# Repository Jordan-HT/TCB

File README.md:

# Thyristor Control Board (TCB) Project
By Jordan Harris-Toovy for internal and shared projects.
This repo contains the design files and accocated C/c++ code for a custom RP2040-powered dual thyristor control module. It is intended to be used to drive either two large SCRs as part of a SCR bridge rectifier, or a single large TriAC as the code of a larger power supply. Via an onboard current sensor, current measurements can be used in a feedback system if desired. Additionally, the I/O on the low-voltage side of the isolation barrier will allow for CNC integration for novel applications.

Currently, the board is in production of the first test batch, with an estimated arrival date of 2023-06-16. Code for the onboard Seeed XIAO RP2040 is also being developed, however, it is not yet ready. I will update this repo with the code and documentation as it is developed.

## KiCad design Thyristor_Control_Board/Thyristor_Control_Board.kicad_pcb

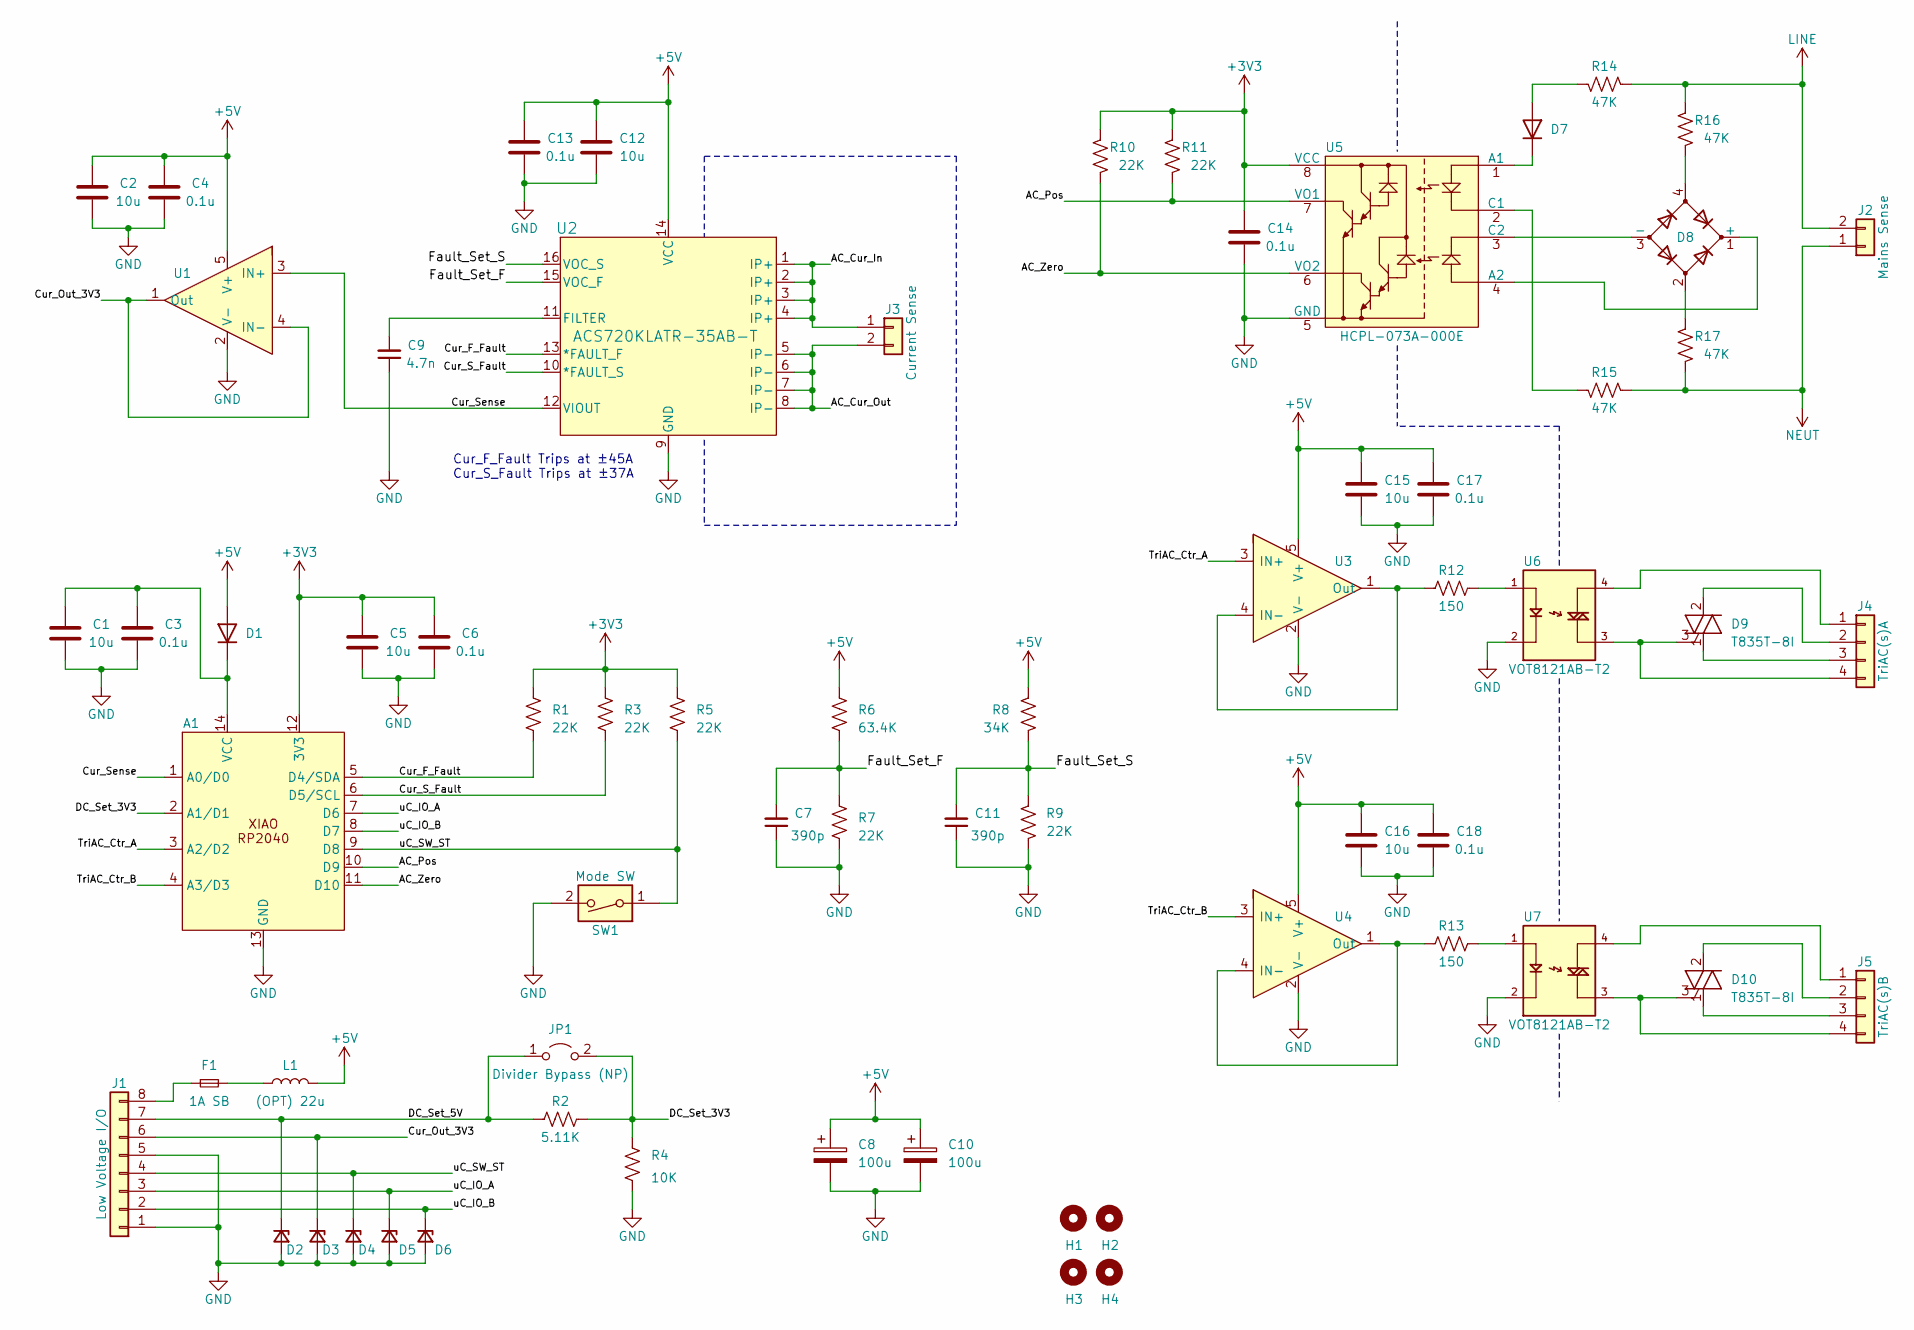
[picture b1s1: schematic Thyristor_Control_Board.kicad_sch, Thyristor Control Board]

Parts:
A1: N/A; seeed_studio_XIAO_RP2040; Part Number 1597-102010428-ND
C1, C2, C5, C12, C15, C16: 10u; C_0805_2012Metric; Part Number CL21B106KOQNNNE
C3, C4, C6, C13, C14, C17, C18: 0.1u; C_0805_2012Metric; Part Number CL21B104KBCNNNC
C7, C11: 390p; C_0805_2012Metric; Part Number C0805C391J5GAC7800
C8, C10: 100u; CP_Radial_D6.3mm_P2.50mm; Part Number A750EK107M1CAAE018
C9: 4.7n; C_0603_1608Metric; Part Number C0603C472K5HAC7867
D1: SS14-LTP; DO-214AC; Part Number SS14-LTP
D2, D3, D4, D5, D6: ESD9X7.0ST5G; D_SOD-923; Part Number ESD9X7.0ST5G
D7: S1M; D_SMA; Part Number S1M
D8: MB10S-13; 4-BESOP; Part Number MB10S-13
D9, D10: T835T-8I; TO-220-3_Vertical; Part Number T835T-8I
F1: 1A SB; Fuse_1206_3216Metric; Part Number 0685T1000-01
H1, H2, H3, H4: MountingHole; MountingHole_2.7mm_M2.5_ISO14580; Part Number NA; Digikey Link NA
J1: Low Voltage I/O; CONN_1985250_PXC; Part Number 1985250
J2: Mains Sense; CONN2_1760490000_WED; Part Number 1760490000
J3: Current Sense; CONN04_VP026584_20P32X18P3_AMP; Part Number VP0265840000G
J4: TriAC(s)A; CONN4_796682-4_TEC; Part Number 796682-4
J5: TriAC(s)B; CONN4_796682-4_TEC; Part Number 796682-4
JP1: Divider Bypass (NP); R_1206_3216Metric_Pad1.30x1.75mm_HandSolder; Part Number RMCF0805ZT0R00
L1: (OPT) 22u; L_Axial_L7.0mm_D3.3mm_P10.16mm_Horizontal_Fastron_MICC; Part Number B78108E1223K009
R1, R3, R5, R7, R9, R10, R11: 22K; R_0805_2012Metric; Part Number RC0805FR-0722KL
R2: 5.11K; R_0805_2012Metric; Part Number RK73H2ATTD5111F
R4: 10K; R_0805_2012Metric; Part Number RK73H2ATTD1002F
R6: 63.4K; R_0805_2012Metric; Part Number RC0805FR-0763K4L
R8: 34K; R_0805_2012Metric; Part Number RC0805FR-0734KL
R12, R13: 150; R_0805_2012Metric; Part Number RC0805FR-07150RL
R14, R15, R16, R17: 47K; R_Axial_DIN0516_L15.5mm_D5.0mm_P20.32mm_Horizontal; Part Number RR03J47KTB
SW1: Mode SW; SW_DS04-254-1-01BK-SMT; Part Number DS04-254-1-01BK-SMT
U1, U3, U4: TLV9301IDBVR; SOT-23-5; Part Number TLV9301IDBVR
U2: ACS720KLATR-35AB-T; 16SOICW-LA; Part Number ACS720KLATR-35AB-T
U5: HCPL-073A-000E; 8-SOIC_3.9mm_Broadcom; Part Number HCPL-073A-000E
U6, U7: VOT8121AB-T2; SOIC254P1016X440-4N; Part Number VOT8121AB-T2

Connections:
+3V3: A1.12 (3V3), C5.2, C6.2, C14.2, R1.1, R3.1, R5.1, R10.1, R11.1, U5.8 (VCC)
+5V: C2.2, C4.2, C8.1, C10.1, C12.2, C13.2, C15.2, C16.2, C17.2, C18.2, D1.2 (A), L1.2, R6.1, R8.1, U1.5 (V+), U2.14 (VCC), U3.5 (V+), U4.5 (V+)
/AC_Cur_In: J3.1, U2.1 (IP+), U2.2 (IP+), U2.3 (IP+), U2.4 (IP+)
/AC_Cur_Out: J3.2, U2.5 (IP-), U2.6 (IP-), U2.7 (IP-), U2.8 (IP-)
/AC_Pos: A1.10 (D9), R11.2, U5.7 (VO1)
/AC_Zero: A1.11 (D10), R10.2, U5.6 (VO2)
/Cur_F_Fault: A1.5 (D4/SDA), R1.2, U2.13 (*FAULT_F)
/Cur_Out_3V3: D3.1 (K), J1.6, U1.1 (Out), U1.4 (IN-)
/Cur_S_Fault: A1.6 (D5/SCL), R3.2, U2.10 (*FAULT_S)
/Cur_Sense: A1.1 (A0/D0), U1.3 (IN+), U2.12 (VIOUT)
/DC_Set_3V3: A1.2 (A1/D1), JP1.2 (B), R2.1, R4.1
/DC_Set_5V: D2.1 (K), J1.7, JP1.1 (A), R2.2
/Fault_Set_F: C7.2, R6.2, R7.1, U2.15 (VOC_F)
/Fault_Set_S: C11.2, R8.2, R9.1, U2.16 (VOC_S)
/TriAC_Ctr_A: A1.3 (A2/D2), U3.3 (IN+)
/TriAC_Ctr_B: A1.4 (A3/D3), U4.3 (IN+)
/uC_IO_A: A1.7 (D6), D5.1 (K), J1.3
/uC_IO_B: A1.8 (D7), D6.1 (K), J1.2
/uC_SW_ST: A1.9 (D8), D4.1 (K), J1.4, R5.2, SW1.1
GND: A1.13 (GND), C1.1, C2.1, C3.1, C4.1, C5.1, C6.1, C7.1, C8.2, C9.1, C10.2, C11.1, C12.1, C13.1, C14.1, C15.1, C16.1, C17.1, C18.1, D2.2 (A), D3.2 (A), D4.2 (A), D5.2 (A), D6.2 (A), J1.1, J1.5, R4.2, R7.2, R9.2, SW1.2, U1.2 (V-), U2.9 (GND), U3.2 (V-), U4.2 (V-), U5.5 (GND), U6.2, U7.2
LINE: J2.2, R14.1, R16.1
NEUT: J2.1, R15.1, R17.2
unnamed: A1.14 (VCC), C1.2, C3.2, D1.1 (K)
unnamed: D7.2 (A), R14.2
unnamed: D7.1 (K), U5.1 (A1)
unnamed: D8.1 (+), U5.4 (A2)
unnamed: D8.3 (-), U5.3 (C2)
unnamed: D8.2, R17.1
unnamed: D8.4, R16.2
unnamed: D9.1 (A1), J4.3
unnamed: D9.2 (A2), J4.2
unnamed: D9.3 (G), J4.4, U6.3
unnamed: D10.1 (A1), J5.3
unnamed: D10.2 (A2), J5.2
unnamed: D10.3 (G), J5.4, U7.3
unnamed: F1.2, L1.1
unnamed: F1.1, J1.8
unnamed: J4.1, U6.4
unnamed: J5.1, U7.4
unnamed: R12.2, U6.1
unnamed: R13.2, U7.1
unnamed: C9.2, U2.11 (FILTER)
unnamed: R12.1, U3.1 (Out), U3.4 (IN-)
unnamed: R13.1, U4.1 (Out), U4.4 (IN-)
unnamed: R15.2, U5.2 (C1)

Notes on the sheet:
Cur_F_Fault Trips at ±45A Cur_S_Fault Trips at ±37A

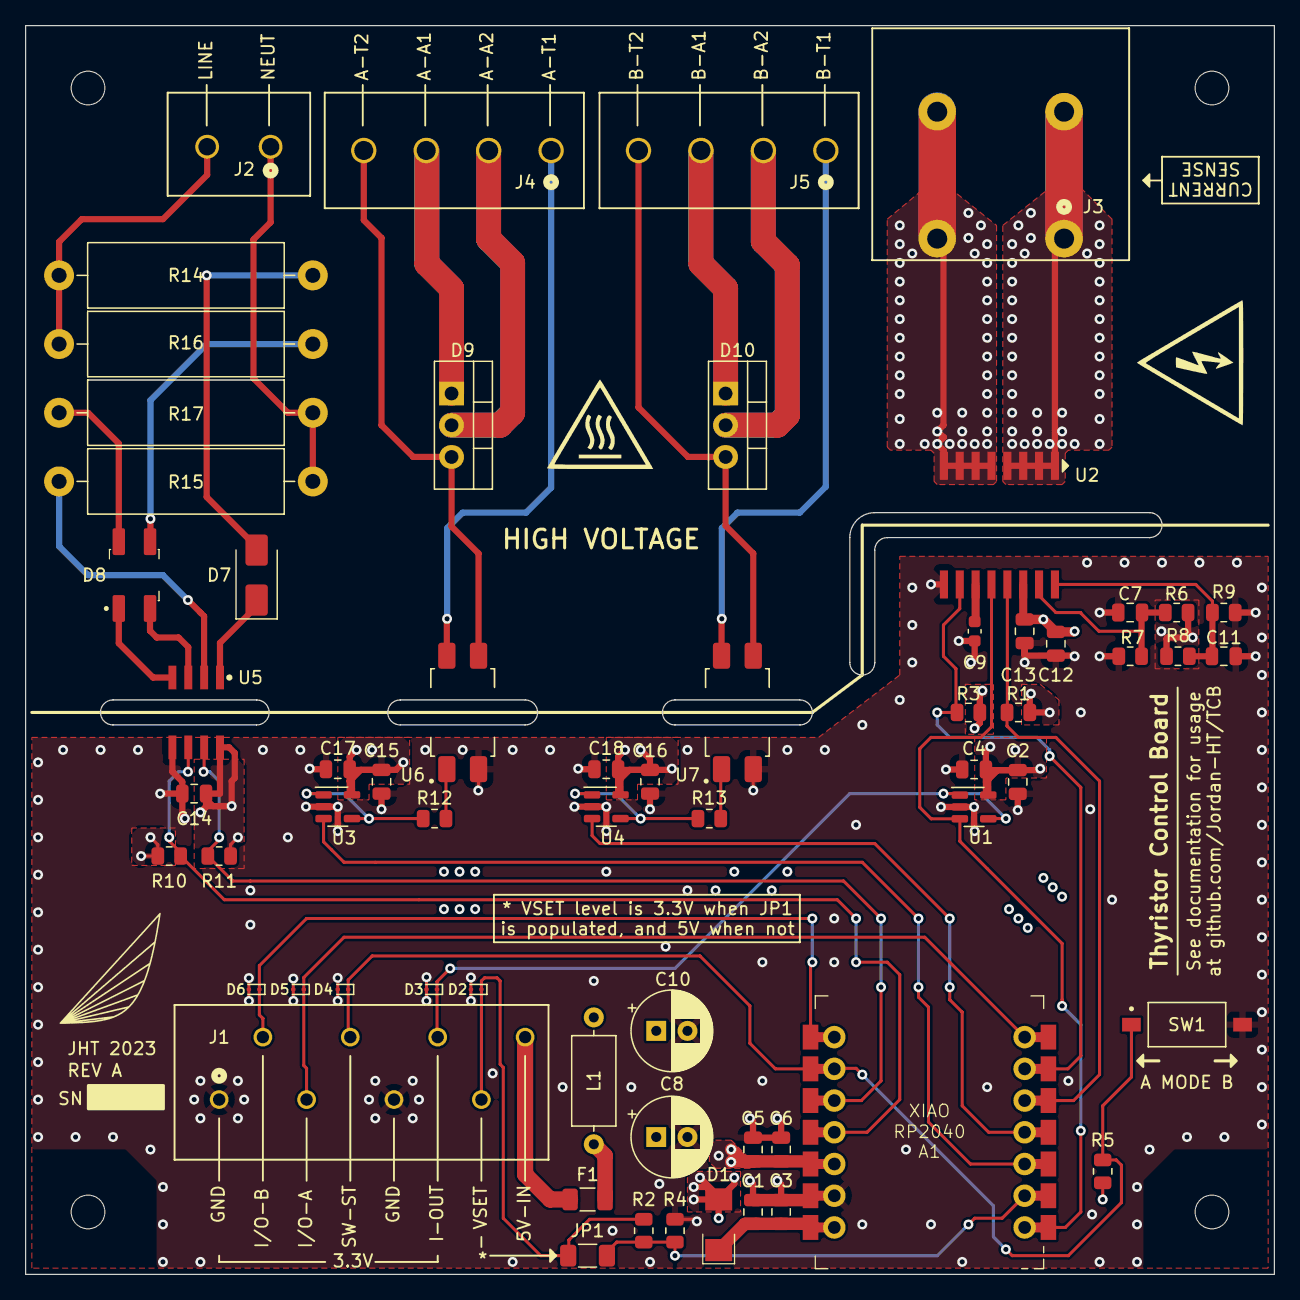
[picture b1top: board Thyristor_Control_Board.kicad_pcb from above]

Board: 4 copper layers, 100.0 x 100.0 mm, 66 parts (0 on the bottom side), 45 nets.

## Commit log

2023-06-09 Added KiCad project & supporting files
    Added the first in-production file set for the PCB.
2023-06-09 Updated README.md with project status and plans
